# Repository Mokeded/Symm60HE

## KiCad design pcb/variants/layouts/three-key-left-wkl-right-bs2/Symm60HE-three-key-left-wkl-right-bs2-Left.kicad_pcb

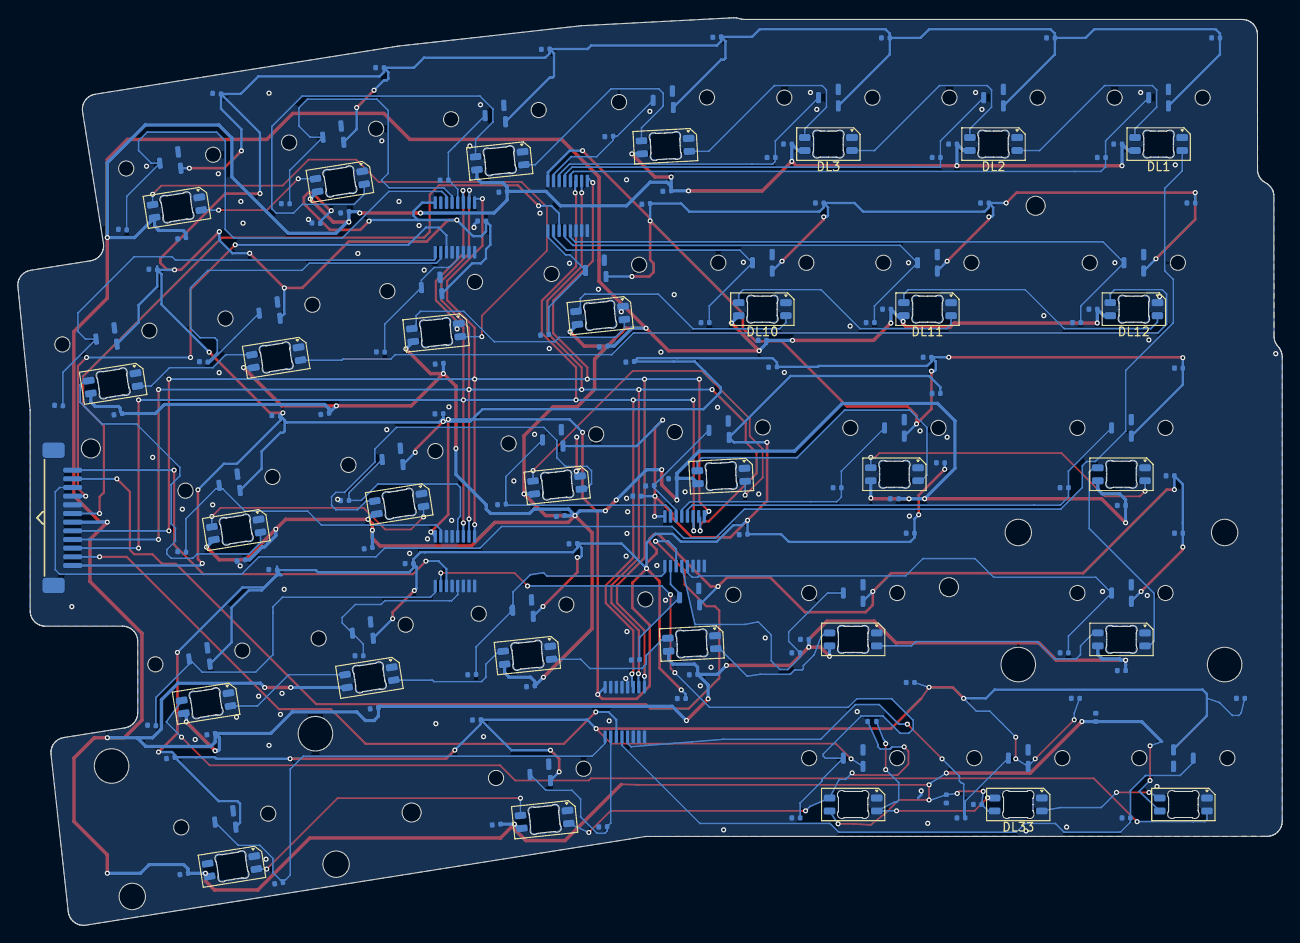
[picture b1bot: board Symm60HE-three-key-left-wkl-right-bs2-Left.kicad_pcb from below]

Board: 2 copper layers, 145.9 x 104.7 mm, 173 parts (167 on the bottom side), 73 nets.

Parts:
AML1, AML2, AML3, AML4, AML5: SN74LV4051A; AM1_TSSOP-16_4.4x5mm_P0.65mm
CL1A, CL2A, CL3A, CL4A, CL5A, CL6A, CL7A, CL8A, CL9A, CL10A, CL11A, CL12A, CL13A, CL14A, CL15A, CL16A, CL17A, CL18A, CL19A, CL20A, CL21A, CL22A, CL23A, CL24A, CL25A, CL26A, CL27A, CL29A, CL31A, CL32A, CL33A: 100n; C1_C_0402_1005Metric
CL1B, CL2B, CL3B, CL4B, CL5B, CL6B, CL7B, CL8B, CL9B, CL10B, CL11B, CL12B, CL13B, CL14B, CL15B, CL16B, CL17B, CL18B, CL19B, CL20B, CL21B, CL22B, CL23B, CL24B, CL25B, CL26B, CL27B, CL29B, CL31B, CL32B, CL33B: 4.7n; C1_C_0402_1005Metric
CML1, CML2, CML3, CML4, CML5: 100n; C1_C_0402_1005Metric
CRGBL1, CRGBL2, CRGBL3, CRGBL4, CRGBL5, CRGBL6, CRGBL7, CRGBL8, CRGBL9, CRGBL10, CRGBL11, CRGBL12, CRGBL13, CRGBL14, CRGBL15, CRGBL16, CRGBL17, CRGBL18, CRGBL19, CRGBL20, CRGBL21, CRGBL22, CRGBL23, CRGBL24, CRGBL25, CRGBL26, CRGBL27, CRGBL29, CRGBL30, CRGBL31, CRGBL33: 100n; C1_C_0402_1005Metric
DL1, DL2, DL3, DL4, DL5, DL6, DL7, DL8, DL9, DL10, DL11, DL12, DL13, DL14, DL15, DL16, DL17, DL18, DL19, DL20, DL21, DL22, DL23, DL24, DL25, DL26, DL27, DL29, DL30, DL31, DL33: SK6812MINI-E; SK6812MINI-E_ReverseMount
HEL1, HEL2, HEL3, HEL4, HEL5, HEL6, HEL7, HEL9, HEL10, HEL11, HEL12, HEL13, HEL14, HEL16, HEL17, HEL18, HEL19, HEL20, HEL22, HEL23, HEL24, HEL25, HEL26, HEL27, HEL29, HEL31: MT9102ET; HE_KEY_1.00u
HEL8, HEL32: MT9102ET; HE_KEY_1.50u
HEL15: MT9102ET; HE_KEY_1.75u
HEL21, HEL33: MT9102ET; HE_KEY_2.25u
JL1: FFC_12P; FFC_12P_1.00mm_TopContact
MHL1, MHL2, MHL3, MHL4: M2_NPTH; MountingHole_2.2mm_M2_NPTH
RBPL29: 0R_DNP; R3_R_0402_1005Metric_DNP
SL1, SL2: STAB_MX; STABILIZER_MX_2U

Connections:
+3V3A: AML1.16, AML2.16, AML3.16, AML4.16, AML5.16, CL1A.1, CL2A.1, CL3A.1, CL4A.1, CL5A.1, CL6A.1, CL7A.1, CL8A.1, CL9A.1, CL10A.1, CL11A.1, CL12A.1, CL13A.1, CL14A.1, CL15A.1, CL16A.1, CL17A.1, CL18A.1, CL19A.1, CL20A.1, CL21A.1, CL22A.1, CL23A.1, CL24A.1, CL25A.1, CL26A.1, CL27A.1, CL29A.1, CL31A.1, CL32A.1, CL33A.1, CML1.1, CML2.1, CML3.1, CML4.1, CML5.1, HEL1.1, HEL2.1, HEL3.1, HEL4.1, HEL5.1, HEL6.1, HEL7.1, HEL8.1, HEL9.1, HEL10.1, HEL11.1, HEL12.1, HEL13.1, HEL14.1, HEL15.1, HEL16.1, HEL17.1, HEL18.1, HEL19.1, HEL20.1, HEL21.1, HEL22.1, HEL23.1, HEL24.1, HEL25.1, HEL26.1, HEL27.1, HEL29.1, HEL31.1, HEL32.1, HEL33.1, JL1.12
ADC_L1: AML1.3, JL1.6
ADC_L2: AML2.3, JL1.4
ADC_L3: AML3.3, JL1.2
ADC_L4: AML4.3, JL1.1
ADC_L5: AML5.3, JL1.11
GND: AML1.6, AML1.7, AML1.8, AML2.4, AML2.6, AML2.7, AML2.8, AML3.6, AML3.7, AML3.8, AML4.4, AML4.6, AML4.7, AML4.8, AML4.13, AML4.14, AML5.6, AML5.7, AML5.8, AML5.12, AML5.13, AML5.14, AML5.15, CL1A.2, CL1B.2, CL2A.2, CL2B.2, CL3A.2, CL3B.2, CL4A.2, CL4B.2, CL5A.2, CL5B.2, CL6A.2, CL6B.2, CL7A.2, CL7B.2, CL8A.2, CL8B.2, CL9A.2, CL9B.2, CL10A.2, CL10B.2, CL11A.2, CL11B.2, CL12A.2, CL12B.2, CL13A.2, CL13B.2, CL14A.2, CL14B.2, CL15A.2, CL15B.2, CL16A.2, CL16B.2, CL17A.2, CL17B.2, CL18A.2, CL18B.2, CL19A.2, CL19B.2, CL20A.2, CL20B.2, CL21A.2, CL21B.2, CL22A.2, CL22B.2, CL23A.2, CL23B.2, CL24A.2, CL24B.2, CL25A.2, CL25B.2, CL26A.2, CL26B.2, CL27A.2, CL27B.2, CL29A.2, CL29B.2, CL31A.2, CL31B.2, CL32A.2, CL32B.2, CL33A.2, CL33B.2, CML1.2, CML2.2, CML3.2, CML4.2, CML5.2, CRGBL1.2, CRGBL2.2, CRGBL3.2, CRGBL4.2, CRGBL5.2, CRGBL6.2, CRGBL7.2, CRGBL8.2, CRGBL9.2, CRGBL10.2, CRGBL11.2, CRGBL12.2, CRGBL13.2, CRGBL14.2, CRGBL15.2, CRGBL16.2, CRGBL17.2, CRGBL18.2, CRGBL19.2, CRGBL20.2, CRGBL21.2, CRGBL22.2, CRGBL23.2, CRGBL24.2, CRGBL25.2, CRGBL26.2, CRGBL27.2, CRGBL29.2, CRGBL30.2, CRGBL31.2, CRGBL33.2, DL1.1, DL2.1, DL3.1, DL4.1, DL5.1, DL6.1, DL7.1, DL8.1, DL9.1, DL10.1, DL11.1, DL12.1, DL13.1, DL14.1, DL15.1, DL16.1, DL17.1, DL18.1, DL19.1, DL20.1, DL21.1, DL22.1, DL23.1, DL24.1, DL25.1, DL26.1, DL27.1, DL29.1, DL30.1, DL31.1, DL33.1, HEL1.2, HEL2.2, HEL3.2, HEL4.2, HEL5.2, HEL6.2, HEL7.2, HEL8.2, HEL9.2, HEL10.2, HEL11.2, HEL12.2, HEL13.2, HEL14.2, HEL15.2, HEL16.2, HEL17.2, HEL18.2, HEL19.2, HEL20.2, HEL21.2, HEL22.2, HEL23.2, HEL24.2, HEL25.2, HEL26.2, HEL27.2, HEL29.2, HEL31.2, HEL32.2, HEL33.2, JL1.5
HE_L01: AML1.12, CL1B.1, HEL1.3
HE_L02: AML1.13, CL2B.1, HEL2.3
HE_L03: AML1.14, CL3B.1, HEL3.3
HE_L04: AML1.15, CL4B.1, HEL4.3
HE_L05: AML2.12, CL5B.1, HEL5.3
HE_L06: AML2.13, CL6B.1, HEL6.3
HE_L07: AML2.14, CL7B.1, HEL7.3
HE_L08: AML1.5, CL8B.1, HEL8.3
HE_L09: AML1.4, CL9B.1, HEL9.3
HE_L10: AML1.2, CL10B.1, HEL10.3
HE_L11: AML1.1, CL11B.1, HEL11.3
HE_L12: AML2.5, CL12B.1, HEL12.3
HE_L13: AML2.2, CL13B.1, HEL13.3
HE_L14: AML2.1, CL14B.1, HEL14.3
HE_L15: AML3.12, CL15B.1, HEL15.3
HE_L16: AML3.13, CL16B.1, HEL16.3
HE_L17: AML3.14, CL17B.1, HEL17.3
HE_L18: AML3.15, CL18B.1, HEL18.3
HE_L19: AML4.12, CL19B.1, HEL19.3
HE_L20: AML4.15, CL20B.1, HEL20.3
HE_L21: AML3.5, CL21B.1, HEL21.3
HE_L22: AML3.4, CL22B.1, HEL22.3
HE_L23: AML3.2, CL23B.1, HEL23.3
HE_L24: AML3.1, CL24B.1, HEL24.3
HE_L25: AML4.5, CL25B.1, HEL25.3
HE_L26: AML4.1, CL26B.1, HEL26.3
HE_L29: AML4.2, CL31B.1, HEL31.3
HE_L30: AML5.2, CL32B.1, HEL32.3
HE_L31: AML5.1, CL33B.1, HEL33.3
HE_L32: AML5.4, CL27B.1, HEL27.3
HE_L33: AML5.5, CL29B.1, HEL29.3
MUX_A0: AML1.11, AML2.11, AML3.11, AML4.11, AML5.11, JL1.10
MUX_A1: AML1.10, AML2.10, AML3.10, AML4.10, AML5.10, JL1.9
MUX_A2: AML1.9, AML2.9, AML3.9, AML4.9, AML5.9, JL1.8
RGB_L: DL1.2, JL1.3
RGB_L_01: DL1.4, DL2.2
RGB_L_02: DL2.4, DL3.2
RGB_L_03: DL3.4, DL4.2
RGB_L_04: DL4.4, DL5.2
RGB_L_05: DL5.4, DL6.2
RGB_L_06: DL6.4, DL7.2
RGB_L_07: DL7.4, DL8.2
RGB_L_08: DL8.4, DL9.2
RGB_L_09: DL9.4, DL10.2
RGB_L_10: DL10.4, DL11.2
RGB_L_11: DL11.4, DL12.2
RGB_L_12: DL12.4, DL13.2
RGB_L_13: DL13.4, DL14.2
RGB_L_14: DL14.4, DL15.2
RGB_L_15: DL15.4, DL16.2
RGB_L_16: DL16.4, DL17.2
RGB_L_17: DL17.4, DL18.2
RGB_L_18: DL18.4, DL19.2
RGB_L_19: DL19.4, DL20.2
RGB_L_20: DL20.4, DL21.2
RGB_L_21: DL21.4, DL22.2
RGB_L_22: DL22.4, DL23.2
RGB_L_23: DL23.4, DL24.2
RGB_L_24: DL24.4, DL25.2
RGB_L_25: DL25.4, DL26.2
RGB_L_26: DL26.4, DL27.2
RGB_L_27: DL27.4, DL33.2
RGB_L_28: DL29.2, DL33.4, RBPL29.1
RGB_L_29: DL29.4, DL30.2, RBPL29.2
RGB_L_30: DL30.4, DL31.2
VBUS: CRGBL1.1, CRGBL2.1, CRGBL3.1, CRGBL4.1, CRGBL5.1, CRGBL6.1, CRGBL7.1, CRGBL8.1, CRGBL9.1, CRGBL10.1, CRGBL11.1, CRGBL12.1, CRGBL13.1, CRGBL14.1, CRGBL15.1, CRGBL16.1, CRGBL17.1, CRGBL18.1, CRGBL19.1, CRGBL20.1, CRGBL21.1, CRGBL22.1, CRGBL23.1, CRGBL24.1, CRGBL25.1, CRGBL26.1, CRGBL27.1, CRGBL29.1, CRGBL30.1, CRGBL31.1, CRGBL33.1, DL1.3, DL2.3, DL3.3, DL4.3, DL5.3, DL6.3, DL7.3, DL8.3, DL9.3, DL10.3, DL11.3, DL12.3, DL13.3, DL14.3, DL15.3, DL16.3, DL17.3, DL18.3, DL19.3, DL20.3, DL21.3, DL22.3, DL23.3, DL24.3, DL25.3, DL26.3, DL27.3, DL29.3, DL30.3, DL31.3, DL33.3, JL1.7
